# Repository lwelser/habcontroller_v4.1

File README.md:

# habcontroller_v4.1
interface board for RPi CM4, terrarium/aquarium controller board for use with reef-pi or terrarium pi

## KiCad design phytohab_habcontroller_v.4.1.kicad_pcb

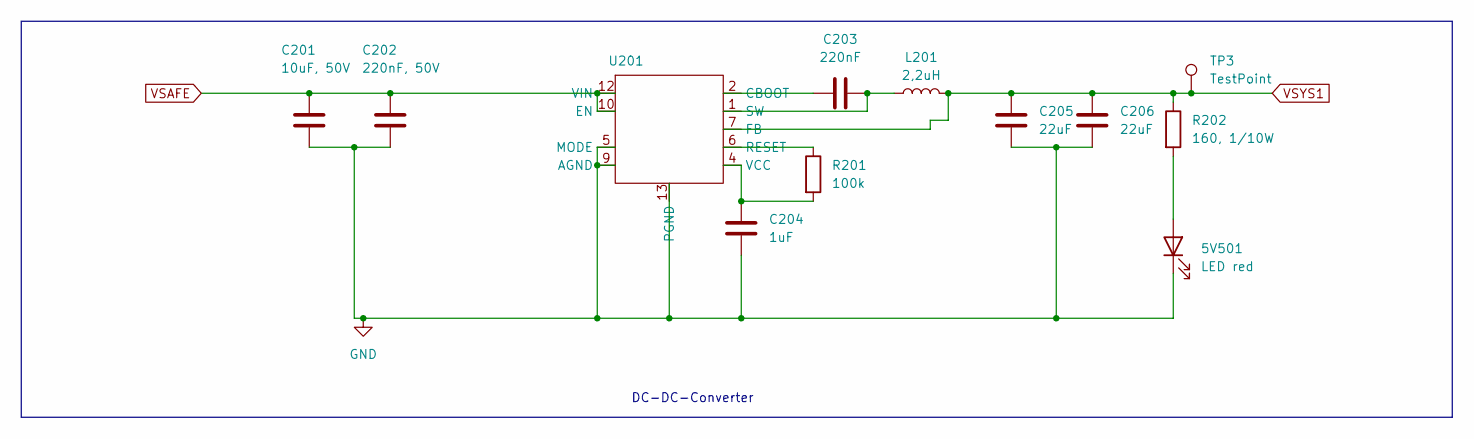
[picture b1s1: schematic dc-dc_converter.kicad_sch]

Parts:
5V501: LED red; LED_0603_1608Metric
C201: 10uF, 50V; C_0805_2012Metric
C202: 220nF, 50V; C_0805_2012Metric
C203: 220nF; C_0402_1005Metric
C204: 1uF; C_0402_1005Metric
C205, C206: 22uF; C_0805_2012Metric
L201: 2,2uH; WE-LHMI_4020
R201: 100k; R_0402_1005Metric
R202: 160, 1/10W; R_0603_1608Metric
TP3: TestPoint; TestPoint_Pad_D1.0mm
U201: LM63635CAQDRRQ1

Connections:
GND: 5V501.1 (K), C201.2, C202.2, C204.2, C205.1, C206.1, U201.5 (MODE), U201.9 (AGND), U201.13 (PGND); also elsewhere on the board
unnamed: 5V501.2 (A), R202.2
unnamed: C203.1, U201.2 (CBOOT)
unnamed: R201.1, U201.6 (RESET)
unnamed: C203.2, L201.1, U201.1 (SW)
unnamed: C204.1, R201.2, U201.4 (VCC)
VSAFE: C201.1, C202.1, U201.10 (EN), U201.12 (VIN); also elsewhere on the board
VSYS1: C205.2, C206.2, L201.2, R202.1, TP3.1, U201.7 (FB); also elsewhere on the board

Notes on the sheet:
DC-DC-Converter

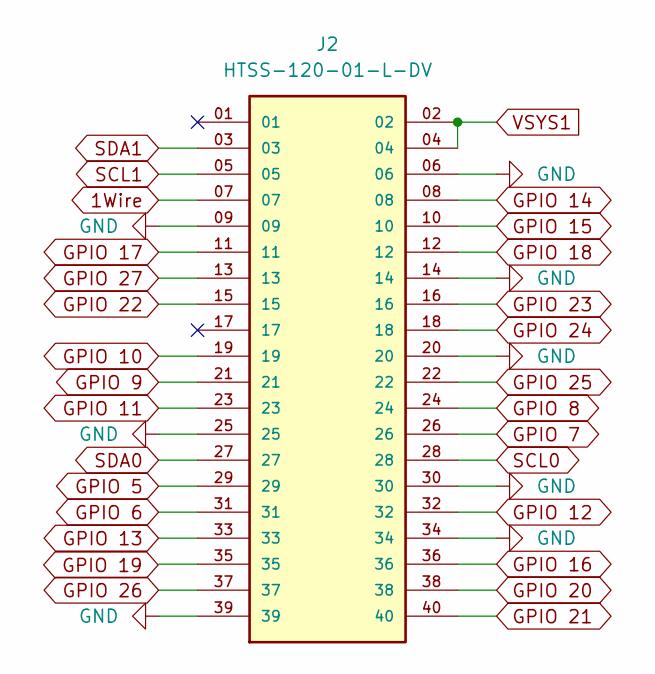
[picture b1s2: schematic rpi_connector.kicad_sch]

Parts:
J2: HTSS-120-01-L-DV; SAMTEC_HTSS-120-01-L-DV; PARTREV R

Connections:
1Wire: J2.07
GND: J2.06, J2.09, J2.14, J2.20, J2.25, J2.30, J2.34, J2.39; also elsewhere on the board
GPIO 5: J2.29
GPIO 6: J2.31
GPIO 7: J2.26
GPIO 8: J2.24
GPIO 9: J2.21
GPIO 10: J2.19
GPIO 11: J2.23
GPIO 12: J2.32
GPIO 13: J2.33
GPIO 14: J2.08
GPIO 15: J2.10
GPIO 16: J2.36
GPIO 17: J2.11
GPIO 18: J2.12
GPIO 20: J2.38
GPIO 21: J2.40
GPIO 22: J2.15
GPIO 23: J2.16
GPIO 24: J2.18
GPIO 25: J2.22
GPIO 26: J2.37
GPIO 27: J2.13
SCL0: J2.28; also elsewhere on the board
SCL1: J2.05; also elsewhere on the board
SDA0: J2.27; also elsewhere on the board
SDA1: J2.03; also elsewhere on the board
VSYS1: J2.02, J2.04; also elsewhere on the board

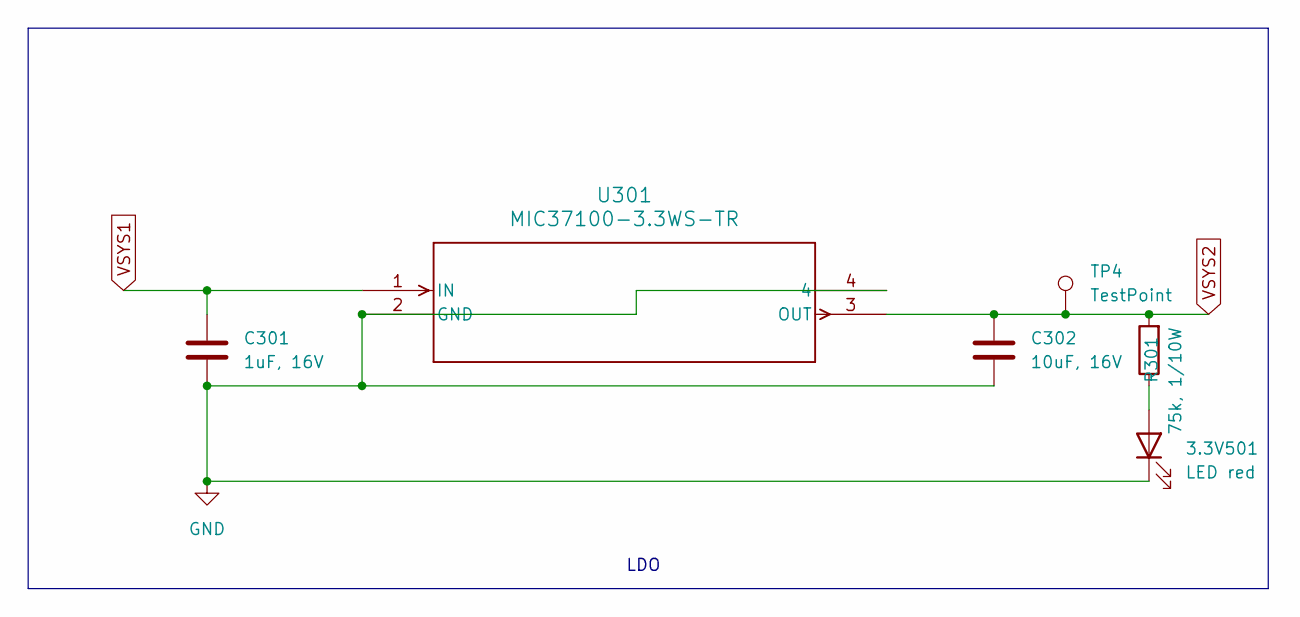
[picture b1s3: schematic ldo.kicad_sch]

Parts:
3.3V501: LED red; LED_0603_1608Metric
C301: 1uF, 16V; C_0805_2012Metric
C302: 10uF, 16V; C_0805_2012Metric
R301: 75k, 1/10W; R_0603_1608Metric
TP4: TestPoint; TestPoint_Pad_D1.0mm
U301: MIC37100-3.3WS-TR; SOT-223_S_MCH

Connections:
GND: 3.3V501.1 (K), C301.2, C302.2, U301.2 (GND), U301.4; also elsewhere on the board
unnamed: 3.3V501.2 (A), R301.1
VSYS1: C301.1, U301.1 (IN); also elsewhere on the board
VSYS2: C302.1, R301.2, TP4.1, U301.3 (OUT); also elsewhere on the board

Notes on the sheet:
LDO

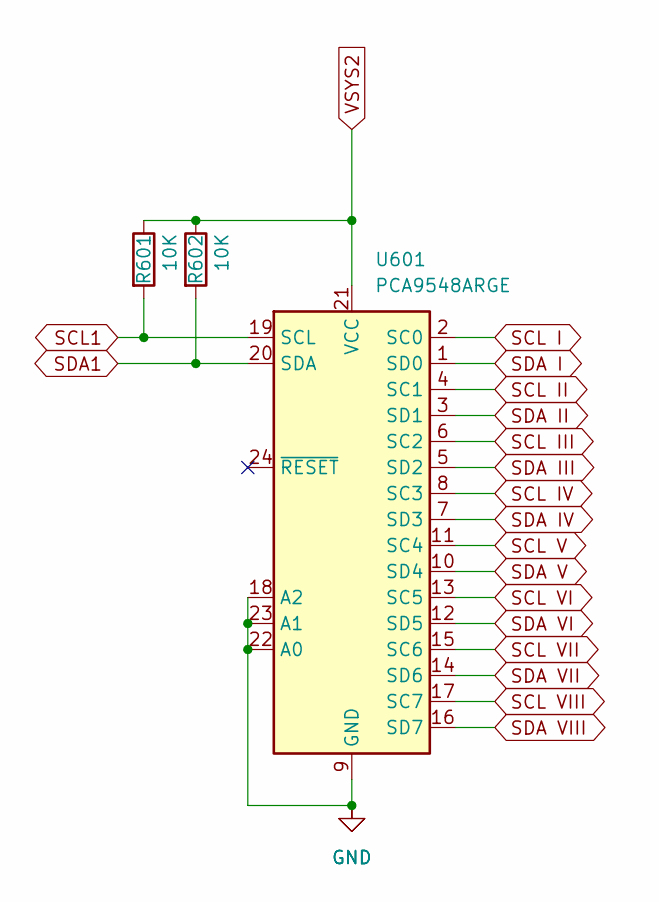
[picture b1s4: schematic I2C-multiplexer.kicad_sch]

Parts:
R601, R602: 10K; R_0402_1005Metric
U601: PCA9548ARGE; Texas_RGE0024C_VQFN-24-1EP_4x4mm_P0.5mm_EP2.1x2.1mm

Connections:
GND: U601.9 (GND), U601.18 (A2), U601.22 (A0), U601.23 (A1); also elsewhere on the board
SCL1: R601.2, U601.19 (SCL); also elsewhere on the board
SCL I: U601.2 (SC0); also elsewhere on the board
SCL II: U601.4 (SC1); also elsewhere on the board
SCL III: U601.6 (SC2); also elsewhere on the board
SCL IV: U601.8 (SC3); also elsewhere on the board
SCL V: U601.11 (SC4); also elsewhere on the board
SCL VI: U601.13 (SC5); also elsewhere on the board
SCL VII: U601.15 (SC6); also elsewhere on the board
SCL VIII: U601.17 (SC7); also elsewhere on the board
SDA1: R602.2, U601.20 (SDA); also elsewhere on the board
SDA I: U601.1 (SD0); also elsewhere on the board
SDA II: U601.3 (SD1); also elsewhere on the board
SDA III: U601.5 (SD2); also elsewhere on the board
SDA IV: U601.7 (SD3); also elsewhere on the board
SDA V: U601.10 (SD4); also elsewhere on the board
SDA VI: U601.12 (SD5); also elsewhere on the board
SDA VII: U601.14 (SD6); also elsewhere on the board
SDA VIII: U601.16 (SD7); also elsewhere on the board
VSYS2: R601.1, R602.1, U601.21 (VCC); also elsewhere on the board

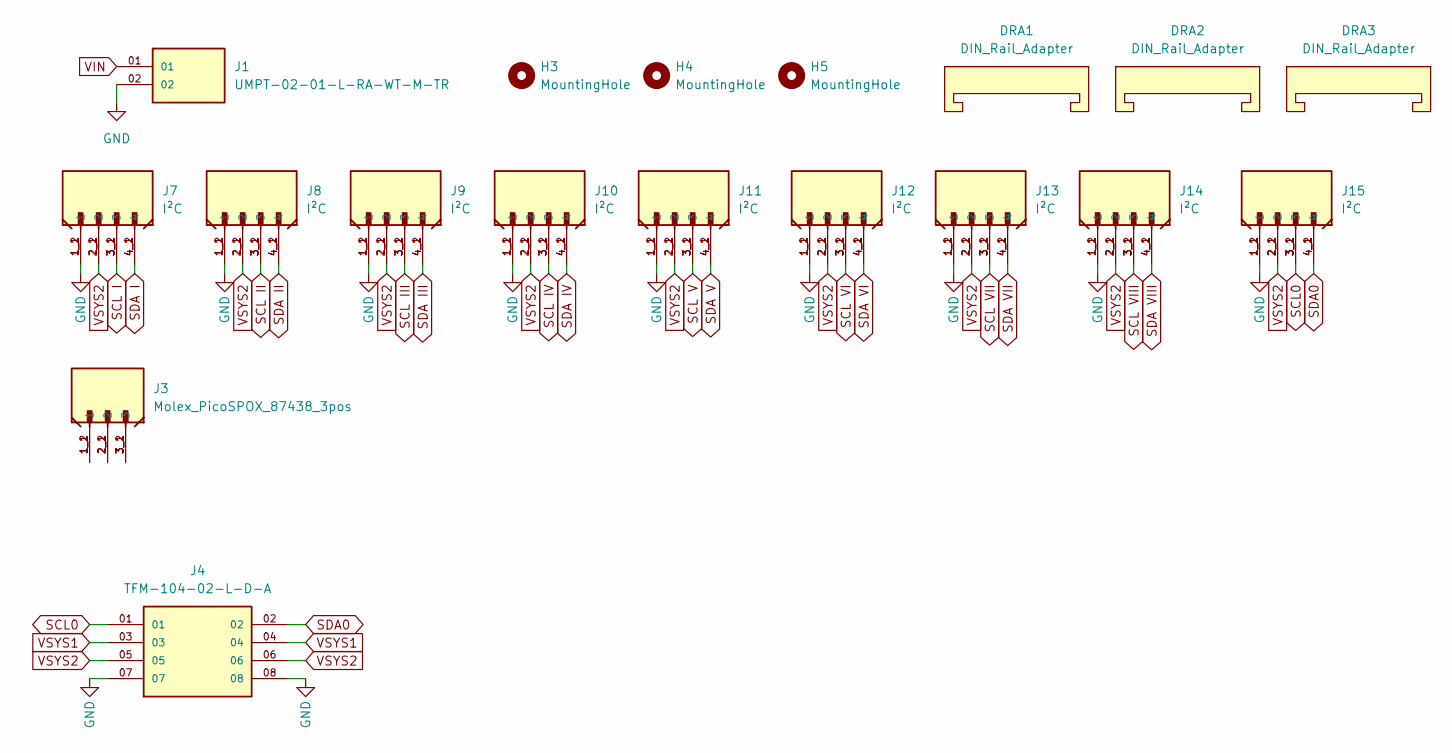
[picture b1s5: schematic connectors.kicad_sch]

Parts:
DRA1, DRA2, DRA3: DIN_Rail_Adapter; DINRailAdapter_3xM3_PhoenixContact_1201578
H3, H4, H5: MountingHole; MountingHole_2.7mm_M2.5_DIN965
J1: UMPT-02-01-L-RA-WT-M-TR; SAMTEC_UMPT-02-01-L-RA-WT-M-TR; PARTREV B
J3: Molex_PicoSPOX_87438_3pos; MOLEX_874380343; PARTREV A; DigiKey_Part_Number WM7647TR-ND
J4: TFM-104-02-L-D-A; SAMTEC_TFM-104-02-L-D-A; PARTREV R
J7, J11, J12, J13, J14, J15: I²C; MOLEX_874380443; PARTREV C; DigiKey_Part_Number WM7648TR-ND
J8, J9, J10: I²C; Molex_PicoSpox_hor_4pos_874380443; PARTREV C; DigiKey_Part_Number WM7648TR-ND

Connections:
GND: J1.02, J4.07, J4.08, J7.1_1 (1), J7.1_2 (1), J8.1_1 (1), J8.1_2 (1), J9.1_1 (1), J9.1_2 (1), J10.1_1 (1), J10.1_2 (1), J11.1_1 (1), J11.1_2 (1), J12.1_1 (1), J12.1_2 (1), J13.1_1 (1), J13.1_2 (1), J14.1_1 (1), J14.1_2 (1), J15.1_1 (1), J15.1_2 (1); also elsewhere on the board
unnamed: J3.1_1 (1), J3.1_2 (1)
unnamed: J3.2_1 (2), J3.2_2 (2)
unnamed: J3.3_1 (3), J3.3_2 (3)
SCL0: J4.01, J15.3_1 (3), J15.3_2 (3); also elsewhere on the board
SCL I: J7.3_1 (3), J7.3_2 (3); also elsewhere on the board
SCL II: J8.3_1 (3), J8.3_2 (3); also elsewhere on the board
SCL III: J9.3_1 (3), J9.3_2 (3); also elsewhere on the board
SCL IV: J10.3_1 (3), J10.3_2 (3); also elsewhere on the board
SCL V: J11.3_1 (3), J11.3_2 (3); also elsewhere on the board
SCL VI: J12.3_1 (3), J12.3_2 (3); also elsewhere on the board
SCL VII: J13.3_1 (3), J13.3_2 (3); also elsewhere on the board
SCL VIII: J14.3_1 (3), J14.3_2 (3); also elsewhere on the board
SDA0: J4.02, J15.4_1 (4), J15.4_2 (4); also elsewhere on the board
SDA I: J7.4_1 (4), J7.4_2 (4); also elsewhere on the board
SDA II: J8.4_1 (4), J8.4_2 (4); also elsewhere on the board
SDA III: J9.4_1 (4), J9.4_2 (4); also elsewhere on the board
SDA IV: J10.4_1 (4), J10.4_2 (4); also elsewhere on the board
SDA V: J11.4_1 (4), J11.4_2 (4); also elsewhere on the board
SDA VI: J12.4_1 (4), J12.4_2 (4); also elsewhere on the board
SDA VII: J13.4_1 (4), J13.4_2 (4); also elsewhere on the board
SDA VIII: J14.4_1 (4), J14.4_2 (4); also elsewhere on the board
VIN: J1.01; also elsewhere on the board
VSYS1: J4.03, J4.04; also elsewhere on the board
VSYS2: J4.05, J4.06, J7.2_1 (2), J7.2_2 (2), J8.2_1 (2), J8.2_2 (2), J9.2_1 (2), J9.2_2 (2), J10.2_1 (2), J10.2_2 (2), J11.2_1 (2), J11.2_2 (2), J12.2_1 (2), J12.2_2 (2), J13.2_1 (2), J13.2_2 (2), J14.2_1 (2), J14.2_2 (2), J15.2_1 (2), J15.2_2 (2); also elsewhere on the board

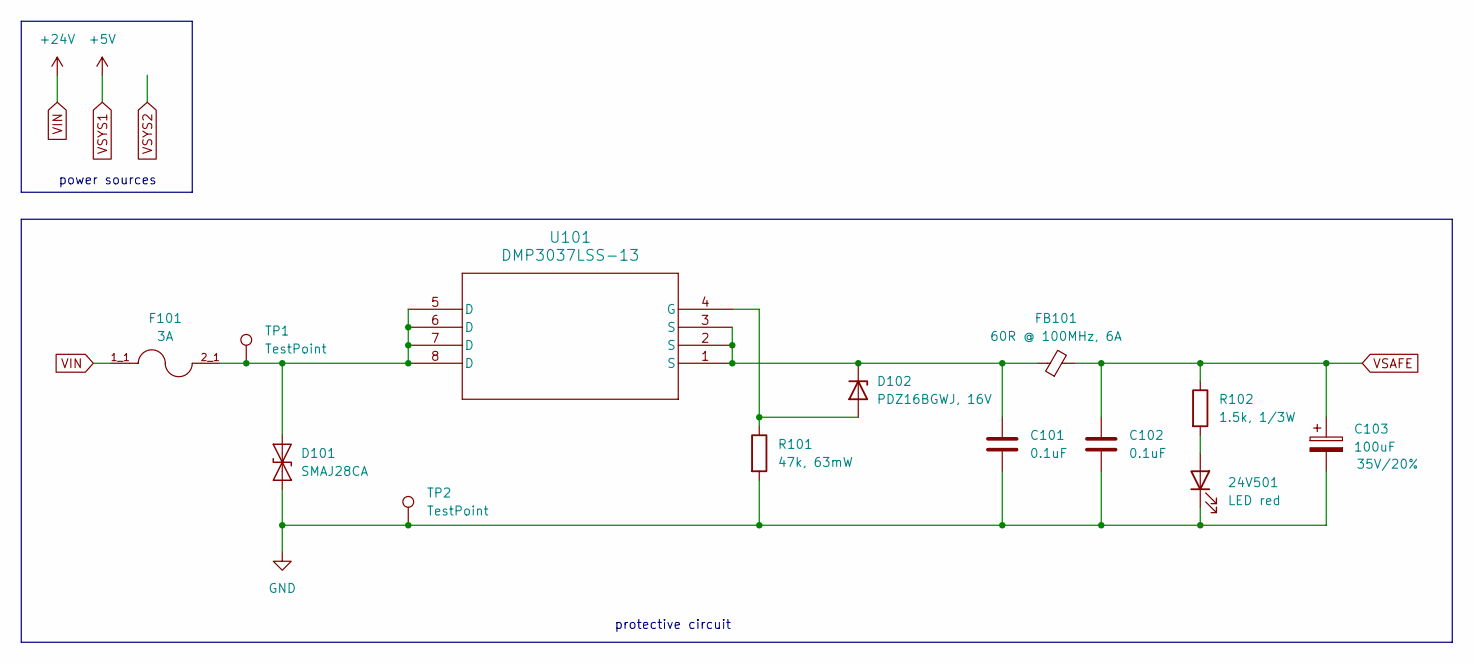
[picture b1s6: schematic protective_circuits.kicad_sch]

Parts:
24V501: LED red; LED_0603_1608Metric
C101, C102: 0.1uF; C_0402_1005Metric
C103: 100uF; CAPAE830X1000N
D101: SMAJ28CA; D_SMA
D102: PDZ16BGWJ, 16V; D_SOD-123
F101: 3A; FUSE_3588; PARTREV E
FB101: 60R @ 100MHz, 6A; BEADC4516X180N
R101: 47k, 63mW; R_0402_1005Metric
R102: 1.5k, 1/3W; R_0603_1608Metric
TP1, TP2: TestPoint; TestPoint_Pad_D1.0mm
U101: DMP3037LSS-13; SO8_DIO

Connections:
GND: 24V501.1 (K), C101.2, C102.2, C103.2, D101.1 (A1), R101.2, TP2.1; also elsewhere on the board
unnamed: 24V501.2 (A), R102.2
unnamed: D101.2 (A2), F101.2_1, TP1.1, U101.5 (D), U101.6 (D), U101.7 (D), U101.8 (D)
unnamed: D102.2 (A), R101.1, U101.4 (G)
unnamed: C101.1, D102.1 (K), FB101.1, U101.1 (S), U101.2 (S), U101.3 (S)
VIN: F101.1_1; also elsewhere on the board
VSAFE: C102.1, C103.1, FB101.2, R102.1; also elsewhere on the board

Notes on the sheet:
protective circuit
power sources

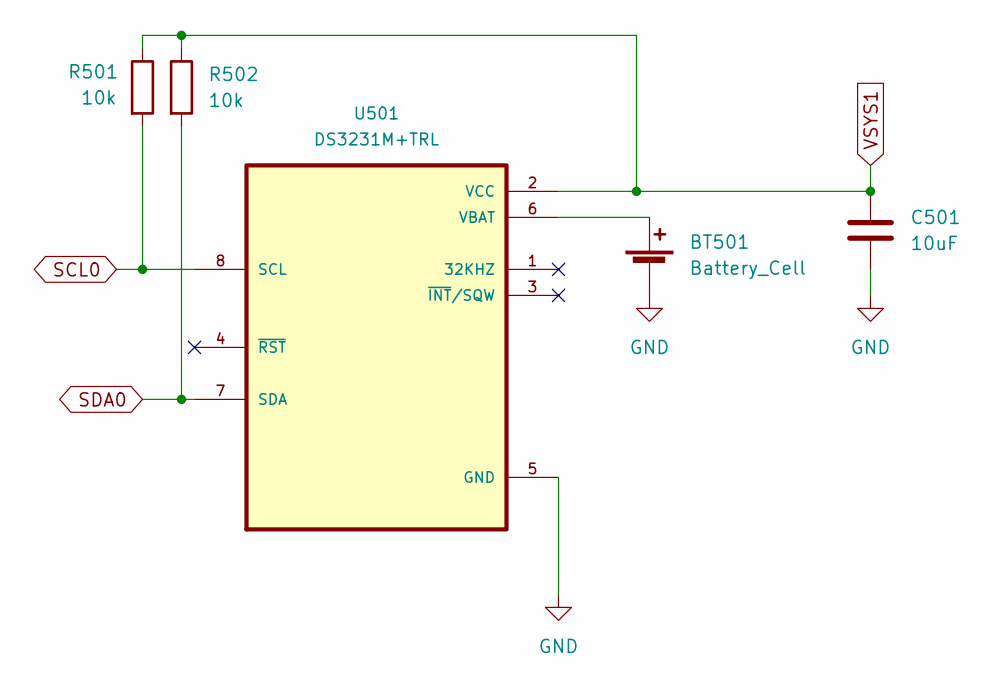
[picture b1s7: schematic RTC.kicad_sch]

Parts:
BT501: Battery_Cell; BH-122A-5
C501: 10uF; C_0603_1608Metric
R501, R502: 10k; R_0603_1608Metric
U501: DS3231M+TRL; SOIC127P600X175-8N

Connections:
GND: BT501.2 (-), C501.2, U501.5 (GND); also elsewhere on the board
unnamed: BT501.1 (+), U501.6 (VBAT)
SCL0: R501.2, U501.8 (SCL); also elsewhere on the board
SDA0: R502.2, U501.7 (SDA); also elsewhere on the board
VSYS1: C501.1, R501.1, R502.1, U501.2 (VCC); also elsewhere on the board

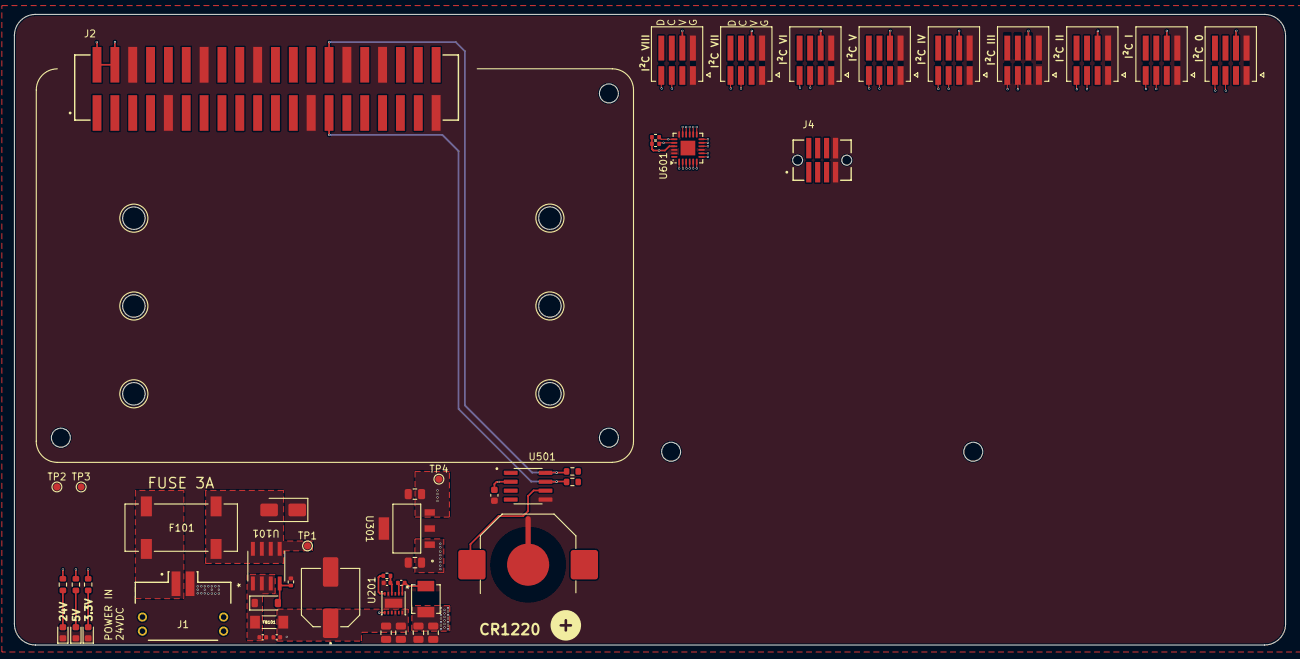
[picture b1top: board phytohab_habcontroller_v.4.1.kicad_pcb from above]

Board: 4 copper layers, 180.9 x 89.8 mm, 59 parts (0 on the bottom side), 36 nets.

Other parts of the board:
H2, H6: MountingHole; MountingHole_2.7mm_M2.5_DIN965

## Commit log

2024-11-09 initial upload
    work in progress on PCB
2024-11-11 Add files via upload
    cleaned up, board outline changed, cons cleaned up,
    GPIO now prepped for breakout board.
2024-11-11 pcb changes
    GPIO-cons routed (what a mess)
2024-11-17 daughterboard created
    divided into mainboard and daughterboard
2024-11-23 CM4>RP3/4
    changed SBC to RP3/4
2024-11-23 prepped for daughterboards
    cons and mounting for GPIO-extension, I²C-ports cleaned up
